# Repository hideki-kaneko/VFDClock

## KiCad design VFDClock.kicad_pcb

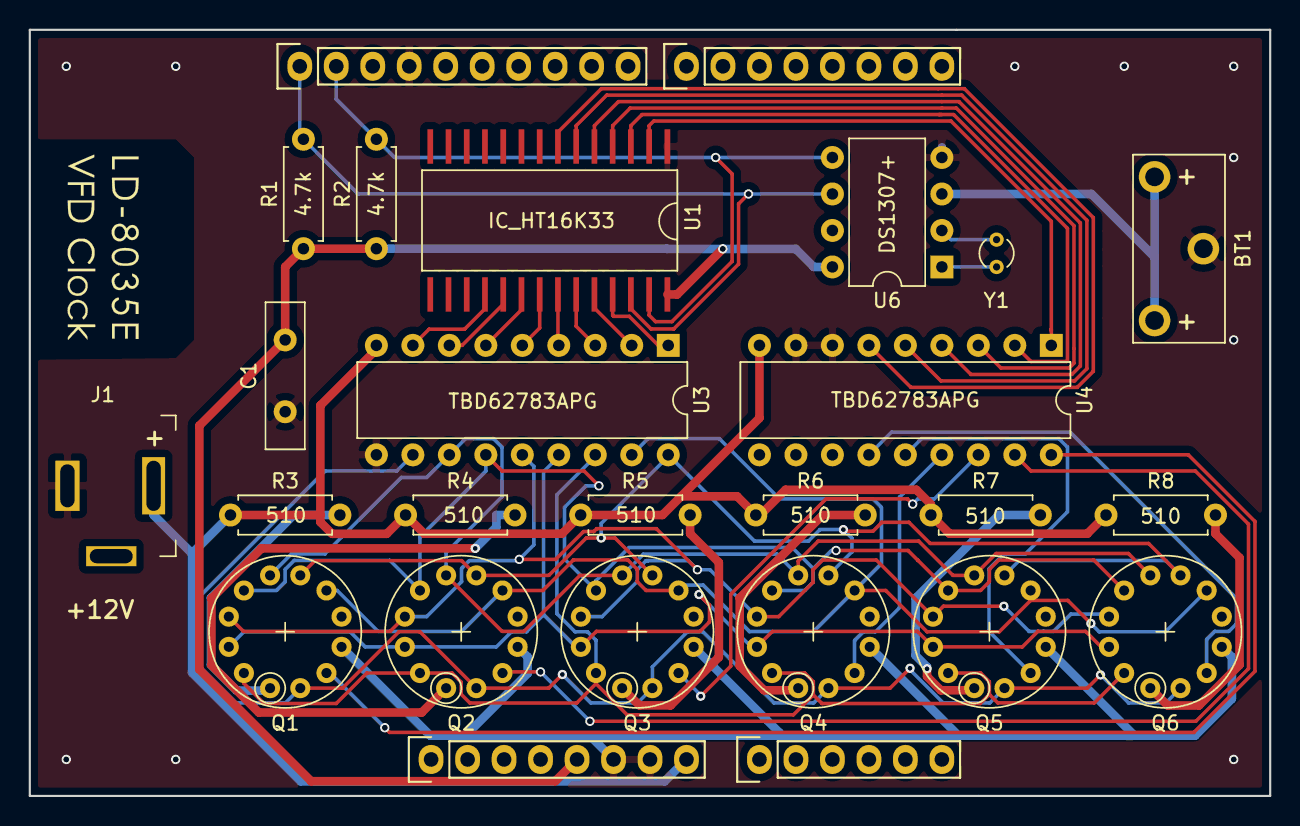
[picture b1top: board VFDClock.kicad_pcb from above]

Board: 2 copper layers, 86.4 x 53.3 mm, 26 parts (0 on the bottom side), 42 nets.

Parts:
BT1: Battery_Cell; Battery_CR2032_CH74-2032LF
C1: 0.1u; C_Disc_D10.0mm_W2.5mm_P5.00mm
J1: Barrel_Jack_MountingPin; DCJack_MJ-179PH
P1: Power; Socket_Strip_Arduino_1x08
P2: Analog; Socket_Strip_Arduino_1x06
P3: Digital; Socket_Strip_Arduino_1x10
P4: Digital; Socket_Strip_Arduino_1x08
Q1, Q2, Q3, Q4, Q5, Q6: VFD_LD8035E
R1, R2: 4.7k; R_Axial_DIN0207_L6.3mm_D2.5mm_P7.62mm_Horizontal
R3, R4, R5, R6, R7, R8: 510; R_Axial_DIN0207_L6.3mm_D2.5mm_P7.62mm_Horizontal
U1: IC_HT16K33
U3, U4: TBD62783APG; DIP-18_W7.62mm
U6: DS1307+; DIP-8_W7.62mm
Y1: 32.768kHz; Crystal_DS26_D2.0mm_L6.0mm_Vertical

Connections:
+5V: C1.1, P1.5, R1.1, R2.1, U1.28, U6.8
+12V: J1.1, P1.8, R3.1, R4.1, R5.1, R6.1, R7.1, R8.1, U3.9, U4.9
+BATT: BT1.1, U6.3
/A4(SDA): P3.2, R2.2, U1.27, U6.5
/A5(SCL): P3.1, R1.2, U1.26, U6.6
/a: Q1.7, Q2.7, Q3.7, Q4.7, Q5.7, Q6.7, U3.18
/b: Q1.6, Q2.6, Q3.6, Q4.6, Q5.6, Q6.6, U3.17
/c: Q1.12, Q2.12, Q3.12, Q4.12, Q5.12, Q6.12, U3.16
/d: Q1.11, Q2.11, Q3.11, Q4.11, Q5.11, Q6.11, U3.15
/dp: Q1.2, Q2.2, Q3.2, Q4.2, Q5.2, Q6.2, U3.11
/e: Q1.10, Q2.10, Q3.10, Q4.10, Q5.10, Q6.10, U3.14
/f: Q1.9, Q2.9, Q3.9, Q4.9, Q5.9, Q6.9, U3.13
/g: Q1.8, Q2.8, Q3.8, Q4.8, Q5.8, Q6.8, U3.12
GND: BT1.2, C1.2, J1.2, P1.6, P1.7, P3.4, Q1.4, Q2.4, Q3.4, Q4.4, Q5.4, Q6.4, U1.1, U3.10, U4.7, U4.8, U4.10, U6.4
unnamed: Q1.1, R3.2
unnamed: Q1.3, U4.18
unnamed: Q2.1, R4.2
unnamed: Q2.3, U4.17
unnamed: Q3.1, R5.2
unnamed: Q3.3, U4.16
unnamed: Q4.1, R6.2
unnamed: Q4.3, U4.15
unnamed: Q5.1, R7.2
unnamed: Q5.3, U4.14
unnamed: Q6.1, R8.2
unnamed: Q6.3, U4.13
unnamed: U1.2, U4.1
unnamed: U1.3, U4.2
unnamed: U1.4, U4.3
unnamed: U1.5, U4.4
unnamed: U1.6, U4.5
unnamed: U1.7, U4.6
unnamed: U1.18, U3.8
unnamed: U1.19, U3.7
unnamed: U1.20, U3.6
unnamed: U1.21, U3.5
unnamed: U1.22, U3.4
unnamed: U1.23, U3.3
unnamed: U1.24, U3.2
unnamed: U1.25, U3.1
unnamed: U6.1, Y1.1
unnamed: U6.2, Y1.2

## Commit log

2020-07-24 VFDとICをつないだ回路を作成
2020-07-24 余分なビアを削除
2020-07-24 RTCを追加
2020-07-24 自動配線
2020-07-24 配線を修正
2020-07-24 GND修正
2020-07-24 綺麗じゃない線を修正
2020-07-24 DCジャックのフットプリントを更新
2020-07-26 駆動用トランジスタアレイを追加
2020-07-26 抵抗値を変更
2020-07-26 フットプリントの関連付けを更新
2020-07-28 未使用ピンの処理
2020-07-29 RTCを置き換え
2020-07-29 部品を仮配置
2020-07-29 ベタ修正
2020-07-30 手で最適化
2020-07-30 ベタ形状を修正
2020-07-30 ロゴなどを追加
2020-07-30 ガーバーファイルを出力
